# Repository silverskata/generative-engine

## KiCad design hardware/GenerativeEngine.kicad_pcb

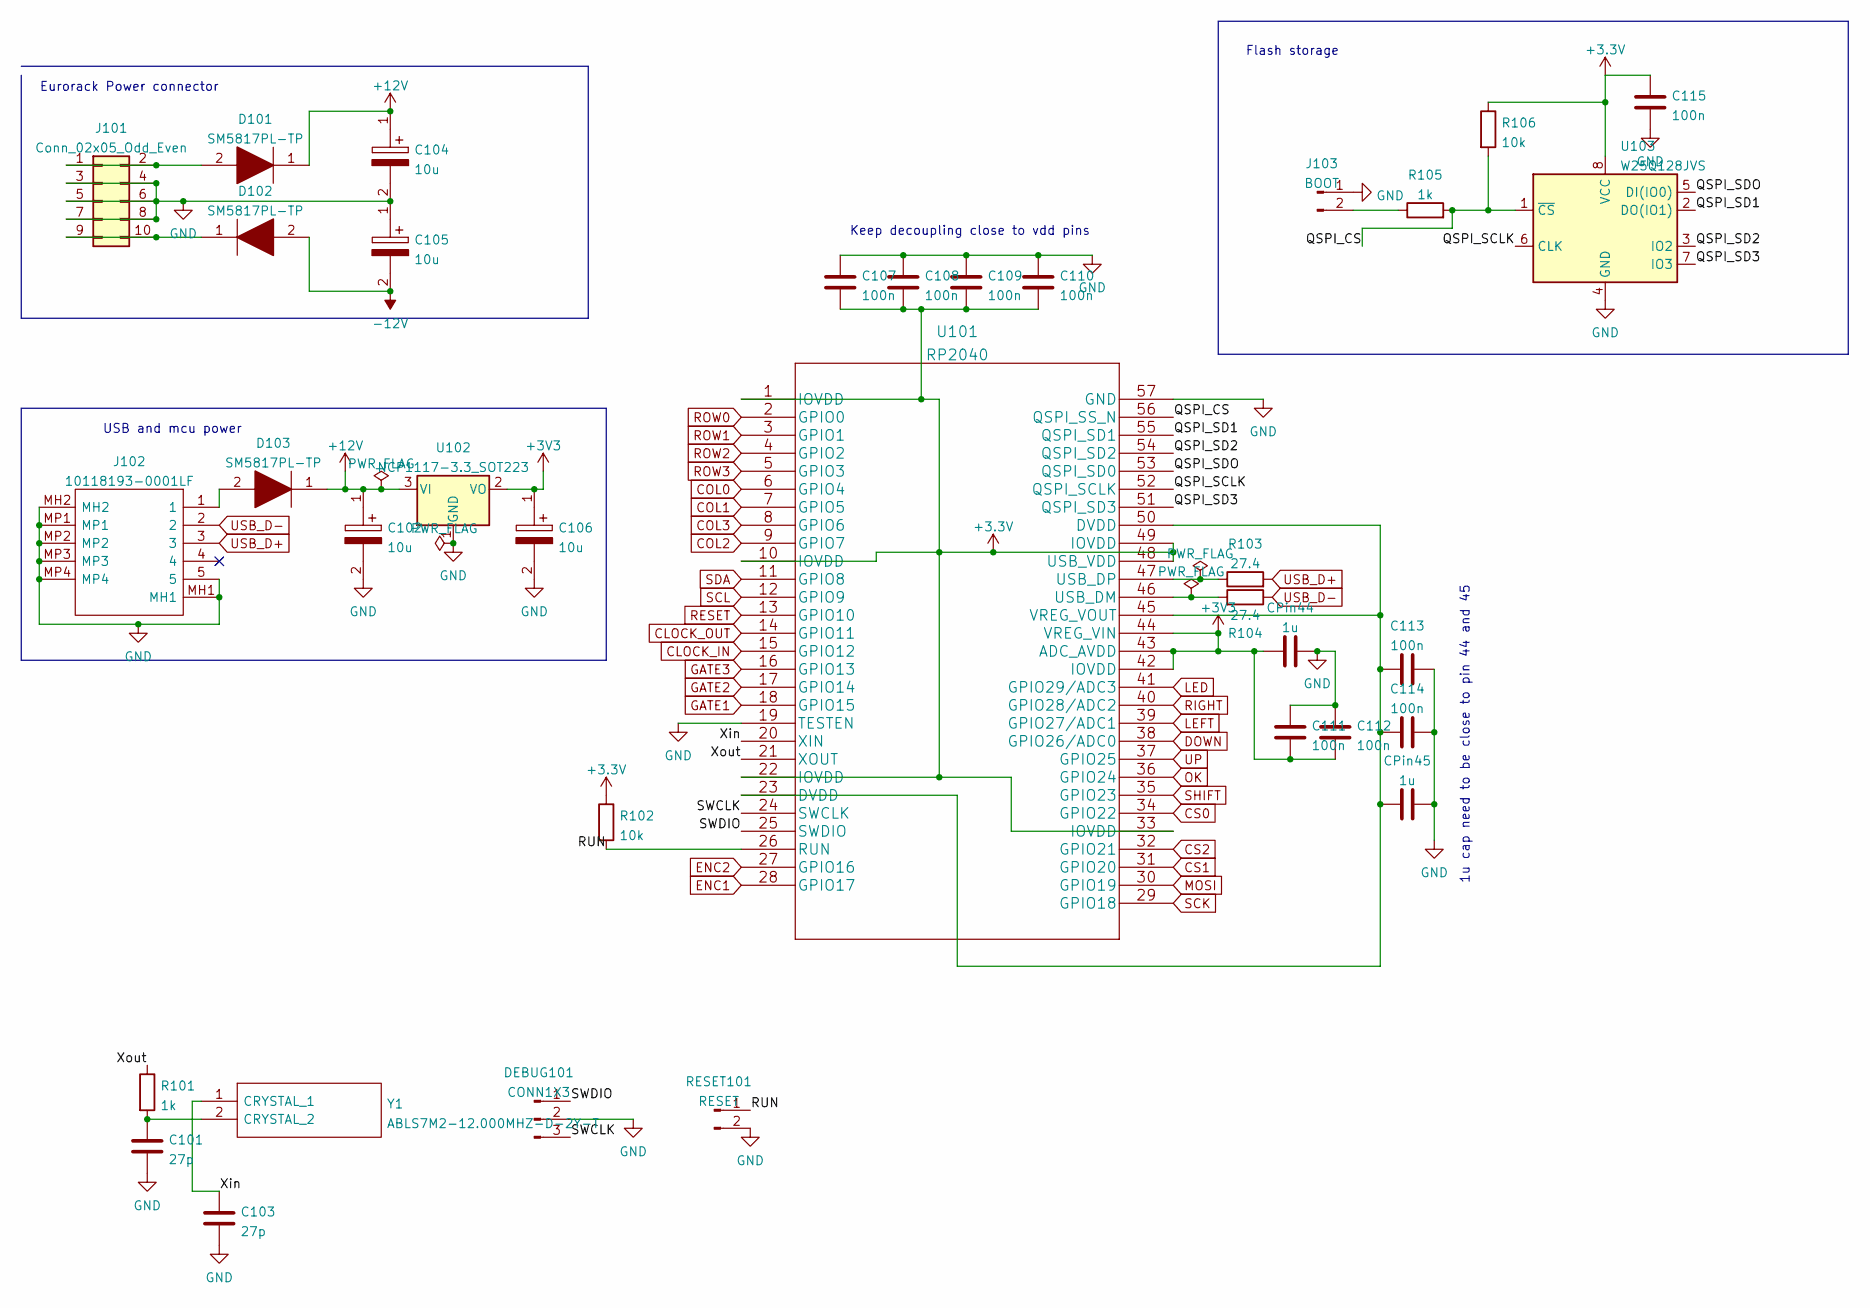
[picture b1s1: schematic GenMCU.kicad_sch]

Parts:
C101, C103: 27p; C_0603_1608Metric_Pad1.08x0.95mm_HandSolder
C102, C104, C105, C106: 10u; CAPAE530X550N; Mouser Part Number 710-865230340001
C107, C108, C109, C110, C111, C112, C113, C114, C115: 100n; C_0603_1608Metric_Pad1.08x0.95mm_HandSolder
CPin44, CPin45: 1u; C_0603_1608Metric_Pad1.08x0.95mm_HandSolder
D101, D102, D103: SM5817PL-TP; SOD3716X120N; Mouser Part Number 833-SM5817PL-TP
DEBUG101: CONN1X3; PinSocket_1x03_P2.54mm_Vertical
J101: Conn_02x05_Odd_Even; PinHeader_2x05_P2.54mm_Vertical
J102: 10118193-0001LF; 101181930001LF; Mouser Part Number 649-10118193-0001LF
J103: BOOT; PinHeader_1x02_P2.54mm_Vertical
R101, R105: 1k; R_0603_1608Metric_Pad0.98x0.95mm_HandSolder
R102, R106: 10k; R_0603_1608Metric_Pad0.98x0.95mm_HandSolder
R103, R104: 27.4; R_0603_1608Metric_Pad0.98x0.95mm_HandSolder
RESET101: RESET; PinHeader_1x02_P2.54mm_Vertical
U101: RP2040
U102: NCP1117-3.3_SOT223; SOT-223-3_TabPin2
U103: W25Q128JVS; SOIC-8_5.23x5.23mm_P1.27mm
Y1: ABLS7M2-12.000MHZ-D-2Y-T; ABLS7M212000MHZD2YT; Mouser Part Number 815-ABLS7M2-12-D-2YT

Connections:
+12V: C102.1, C104.1, D101.1, D103.1, U102.3 (VI); also elsewhere on the board
-12V: C105.2, D102.2; also elsewhere on the board
/GenMCU/QSPI_CS: R105.2, R106.2, U101.56 (QSPI_SS_N), U103.1 (~CS)
/GenMCU/QSPI_SCLK: U101.52 (QSPI_SCLK), U103.6 (CLK)
/GenMCU/QSPI_SD1: U101.55 (QSPI_SD1), U103.2 (DO(IO1))
/GenMCU/QSPI_SD2: U101.54 (QSPI_SD2), U103.3 (IO2)
/GenMCU/QSPI_SD3: U101.51 (QSPI_SD3), U103.7 (IO3)
/GenMCU/QSPI_SDO: U101.53 (QSPI_SD0), U103.5 (DI(IO0))
/GenMCU/RUN: R102.2, RESET101.1, U101.26 (RUN); also elsewhere on the board
/GenMCU/SWCLK: DEBUG101.3, U101.24 (SWCLK); also elsewhere on the board
/GenMCU/SWDIO: DEBUG101.1, U101.25 (SWDIO); also elsewhere on the board
/GenMCU/Xin: C103.1, U101.20 (XIN), Y1.1 (CRYSTAL)
/GenMCU/Xout: R101.1, U101.21 (XOUT)
CLOCK_IN: U101.15 (GPIO12); also elsewhere on the board
CLOCK_OUT: U101.14 (GPIO11); also elsewhere on the board
COL0: U101.6 (GPIO4); also elsewhere on the board
COL1: U101.7 (GPIO5); also elsewhere on the board
COL2: U101.9 (GPIO7); also elsewhere on the board
COL3: U101.8 (GPIO6); also elsewhere on the board
CS0: U101.34 (GPIO22); also elsewhere on the board
CS1: U101.31 (GPIO20); also elsewhere on the board
CS2: U101.32 (GPIO21); also elsewhere on the board
DOWN: U101.38 (GPIO26/ADC0); also elsewhere on the board
ENC1: U101.28 (GPIO17); also elsewhere on the board
ENC2: U101.27 (GPIO16); also elsewhere on the board
GATE1: U101.18 (GPIO15); also elsewhere on the board
GATE2: U101.17 (GPIO14); also elsewhere on the board
GATE3: U101.16 (GPIO13); also elsewhere on the board
GND: C101.2, C102.2, C103.2, C104.2, C105.1, C106.2, C107.1, C108.1, C109.1, C110.1, C111.1, C112.1, C113.2, C114.2, C115.2, CPin44.2, CPin45.2, DEBUG101.2, J101.3, J101.4, J101.5, J101.6, J101.7, J101.8, J102.5, J102.MH1, J102.MH2, J102.MP1, J102.MP2, J102.MP3, J102.MP4, J103.1, RESET101.2, U101.19 (TESTEN), U101.57 (GND), U102.1 (GND), U103.4 (GND); also elsewhere on the board
LED: U101.41 (GPIO29/ADC3); also elsewhere on the board
LEFT: U101.39 (GPIO27/ADC1); also elsewhere on the board
MOSI: U101.30 (GPIO19); also elsewhere on the board
unnamed: C101.1, R101.2, Y1.2 (CRYSTAL)
unnamed: C113.1, C114.1, CPin45.1, U101.23 (DVDD), U101.45 (VREG_VOUT), U101.50 (DVDD)
unnamed: D101.2, J101.1, J101.2
unnamed: D102.1, J101.9, J101.10
unnamed: D103.2, J102.1
unnamed 67: J103.2, R105.1; also elsewhere on the board
unnamed: R103.1, U101.47 (USB_DP)
unnamed: R104.2, U101.46 (USB_DM)
OK: U101.36 (GPIO24); also elsewhere on the board
RESET: U101.13 (GPIO10); also elsewhere on the board
RIGHT: U101.40 (GPIO28/ADC2); also elsewhere on the board
ROW0: U101.2 (GPIO0); also elsewhere on the board
ROW1: U101.3 (GPIO1); also elsewhere on the board
ROW2: U101.4 (GPIO2); also elsewhere on the board
ROW3: U101.5 (GPIO3); also elsewhere on the board
SCK: U101.29 (GPIO18); also elsewhere on the board
SCL: U101.12 (GPIO9); also elsewhere on the board
SDA: U101.11 (GPIO8); also elsewhere on the board
SHIFT: U101.35 (GPIO23); also elsewhere on the board
UP: U101.37 (GPIO25); also elsewhere on the board
USB_D+: J102.3, R103.2
USB_D-: J102.2, R104.1

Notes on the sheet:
USB and mcu power
1u cap need to be close to pin 44 and 45
Flash storage
Eurorack Power connector
Keep decoupling close to vdd pins

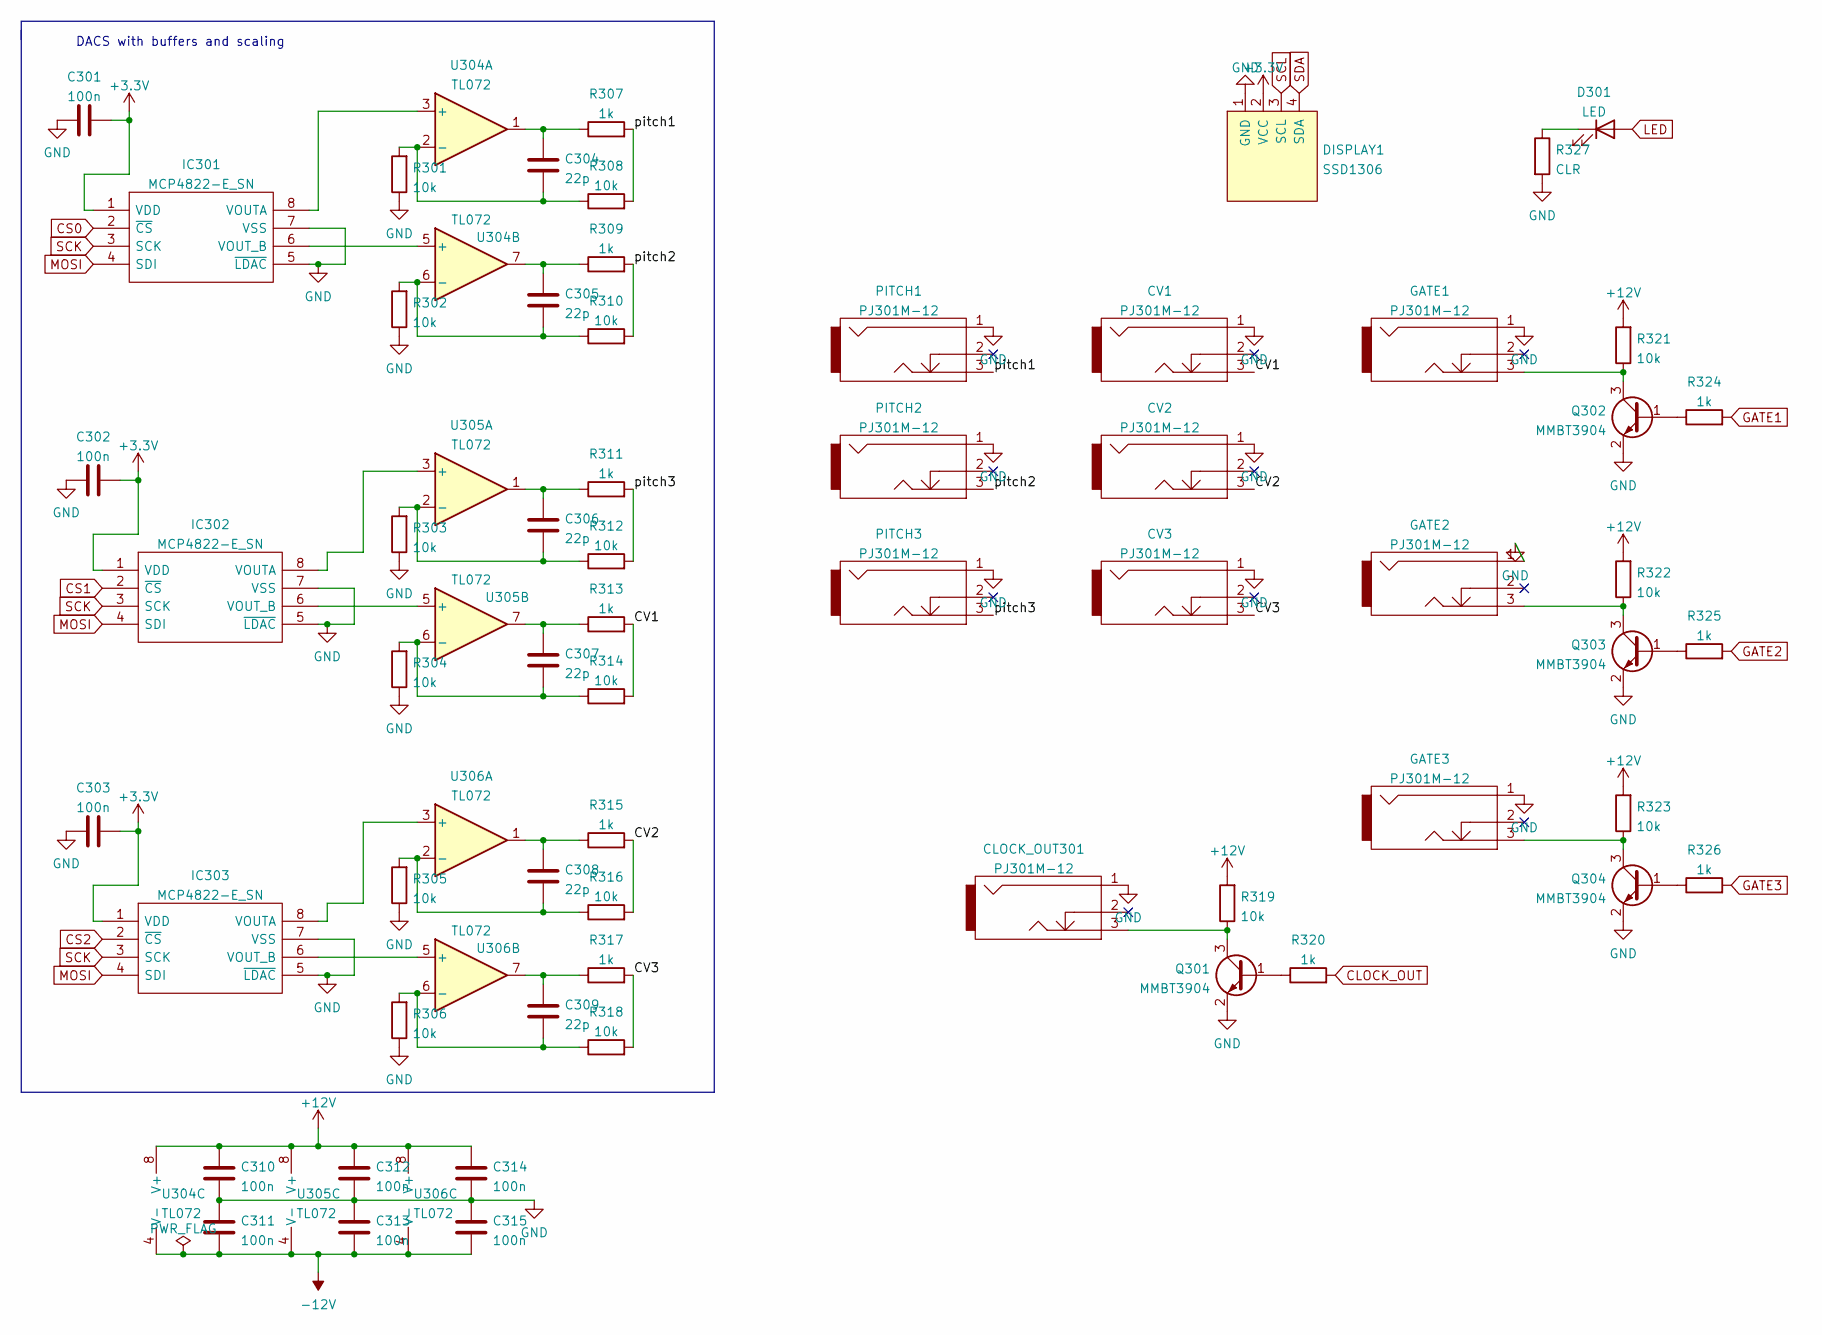
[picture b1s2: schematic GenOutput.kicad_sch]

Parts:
C301, C302, C303, C310, C311, C312, C313, C314, C315: 100n; C_0603_1608Metric_Pad1.08x0.95mm_HandSolder
C304, C305, C306, C307, C308, C309: 22p; C_0603_1608Metric_Pad1.08x0.95mm_HandSolder
CLOCK_OUT301: PJ301M-12
CV1, CV2, CV3: PJ301M-12
D301: LED; LED_D3.0mm
DISPLAY1: SSD1306; 128x64OLED
GATE1, GATE2, GATE3: PJ301M-12
IC301, IC302, IC303: MCP4822-E_SN; SOIC127P600X175-8N; Mouser Part Number 579-MCP4822-E/SN
PITCH1, PITCH2, PITCH3: PJ301M-12
Q301, Q302, Q303, Q304: MMBT3904; SOT-23
R301, R302, R303, R304, R305, R306, R308, R310, R312, R314, R316, R318, R319, R321, R322, R323: 10k; R_0603_1608Metric_Pad0.98x0.95mm_HandSolder
R307, R309, R311, R313, R315, R317, R320, R324, R325, R326: 1k; R_0603_1608Metric_Pad0.98x0.95mm_HandSolder
R327: CLR; R_0603_1608Metric_Pad0.98x0.95mm_HandSolder
U304, U305, U306: TL072; SOIC-8_3.9x4.9mm_P1.27mm

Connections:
+12V: C310.1, C312.1, C314.1, R319.2, R321.2, R322.2, R323.2, U304.8 (V+), U305.8 (V+), U306.8 (V+); also elsewhere on the board
-12V: C311.2, C313.2, C315.2, U304.4 (V-), U305.4 (V-), U306.4 (V-); also elsewhere on the board
/GenOutput/CV1: CV1.3, R313.2, R314.2
/GenOutput/CV2: CV2.3, R315.2, R316.2
/GenOutput/CV3: CV3.3, R317.2, R318.2
/GenOutput/pitch1: PITCH1.3, R307.2, R308.2
/GenOutput/pitch2: PITCH2.3, R309.2, R310.2
/GenOutput/pitch3: PITCH3.3, R311.2, R312.2
CLOCK_OUT: R320.2; also elsewhere on the board
CS0: IC301.2 (~CS); also elsewhere on the board
CS1: IC302.2 (~CS); also elsewhere on the board
CS2: IC303.2 (~CS); also elsewhere on the board
GATE1: R324.2; also elsewhere on the board
GATE2: R325.2; also elsewhere on the board
GATE3: R326.2; also elsewhere on the board
GND: C301.1, C302.1, C303.1, C310.2, C311.1, C312.2, C313.1, C314.2, C315.1, CLOCK_OUT301.1, CV1.1, CV2.1, CV3.1, DISPLAY1.1 (GND), GATE1.1, GATE2.1, GATE3.1, IC301.5 (~LDAC), IC301.7 (VSS), IC302.5 (~LDAC), IC302.7 (VSS), IC303.5 (~LDAC), IC303.7 (VSS), PITCH1.1, PITCH2.1, PITCH3.1, Q301.2 (E), Q302.2 (E), Q303.2 (E), Q304.2 (E), R301.1, R302.1, R303.1, R304.1, R305.1, R306.1, R327.2; also elsewhere on the board
LED: D301.2 (A); also elsewhere on the board
MOSI: IC301.4 (SDI), IC302.4 (SDI), IC303.4 (SDI); also elsewhere on the board
unnamed: C304.1, R307.1, U304.1
unnamed: C304.2, R301.2, R308.1, U304.2 (-)
unnamed: C305.1, R309.1, U304.7
unnamed: C305.2, R302.2, R310.1, U304.6 (-)
unnamed: C306.1, R311.1, U305.1
unnamed: C306.2, R303.2, R312.1, U305.2 (-)
unnamed: C307.1, R313.1, U305.7
unnamed: C307.2, R304.2, R314.1, U305.6 (-)
unnamed: C308.1, R315.1, U306.1
unnamed: C308.2, R305.2, R316.1, U306.2 (-)
unnamed: C309.1, R317.1, U306.7
unnamed: C309.2, R306.2, R318.1, U306.6 (-)
unnamed 53: CLOCK_OUT301.3, Q301.3 (C), R319.1; also elsewhere on the board
unnamed: D301.1 (K), R327.1
unnamed: GATE1.3, Q302.3 (C), R321.1
unnamed: GATE2.3, Q303.3 (C), R322.1
unnamed: GATE3.3, Q304.3 (C), R323.1
unnamed: IC301.6 (VOUT_B), U304.5 (+)
unnamed: IC301.8 (VOUTA), U304.3 (+)
unnamed: IC302.6 (VOUT_B), U305.5 (+)
unnamed: IC302.8 (VOUTA), U305.3 (+)
unnamed: IC303.6 (VOUT_B), U306.5 (+)
unnamed: IC303.8 (VOUTA), U306.3 (+)
unnamed: Q301.1 (B), R320.1
unnamed: Q302.1 (B), R324.1
unnamed: Q303.1 (B), R325.1
unnamed: Q304.1 (B), R326.1
SCK: IC301.3 (SCK), IC302.3 (SCK), IC303.3 (SCK); also elsewhere on the board

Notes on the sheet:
DACS with buffers and scaling

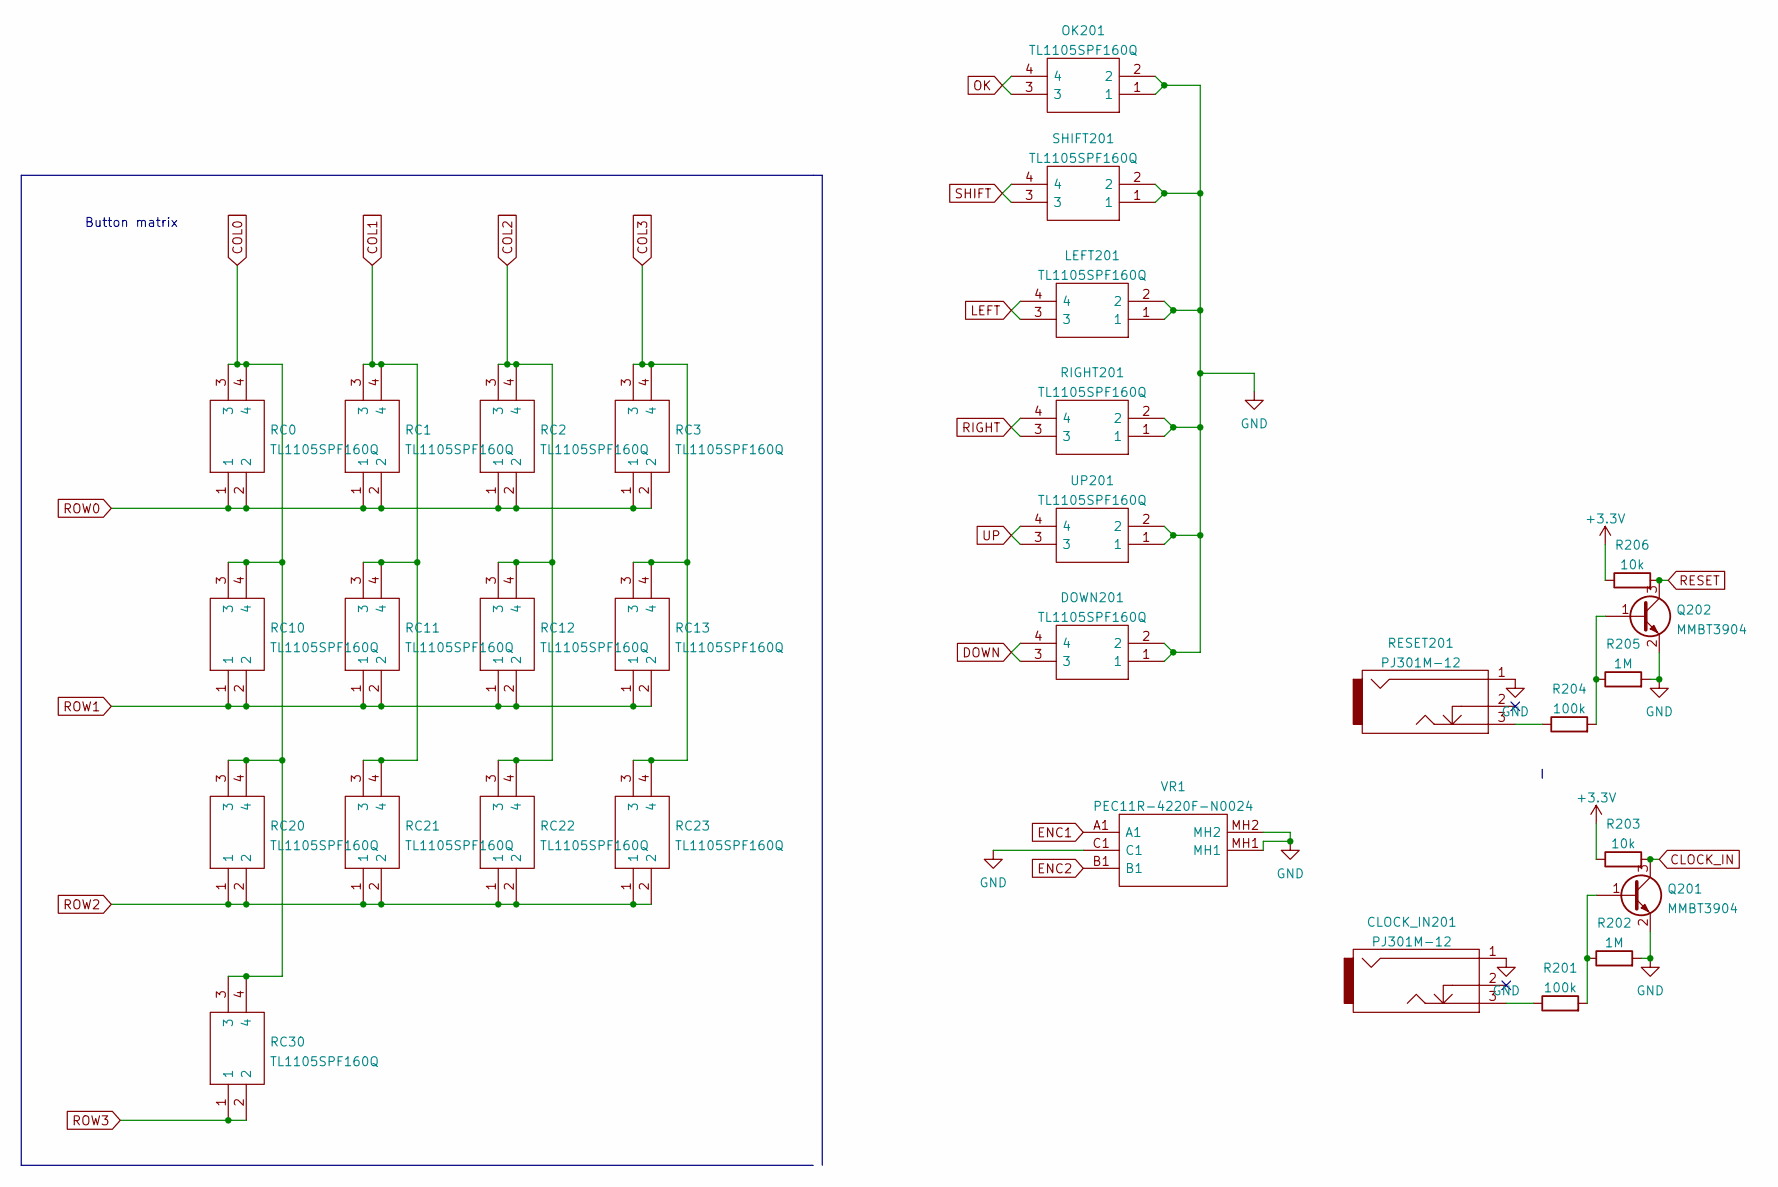
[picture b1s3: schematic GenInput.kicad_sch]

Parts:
CLOCK_IN201: PJ301M-12
DOWN201: TL1105SPF160Q; Mouser Part Number 612-TL1105SP
LEFT201: TL1105SPF160Q; Mouser Part Number 612-TL1105SP
OK201: TL1105SPF160Q; Mouser Part Number 612-TL1105SP
Q201, Q202: MMBT3904; SOT-23
R201, R204: 100k; R_0603_1608Metric_Pad0.98x0.95mm_HandSolder
R202, R205: 1M; R_0603_1608Metric_Pad0.98x0.95mm_HandSolder
R203, R206: 10k; R_0603_1608Metric_Pad0.98x0.95mm_HandSolder
RC0, RC1, RC2, RC3, RC10, RC11, RC12, RC13, RC20, RC21, RC22, RC23, RC30: TL1105SPF160Q; Mouser Part Number 612-TL1105SP
RESET201: PJ301M-12
RIGHT201: TL1105SPF160Q; Mouser Part Number 612-TL1105SP
SHIFT201: TL1105SPF160Q; Mouser Part Number 612-TL1105SP
UP201: TL1105SPF160Q; Mouser Part Number 612-TL1105SP
VR1: PEC11R-4220F-N0024; PEC11R4215FN0012; Mouser Part Number 652-PEC11R-4220F-N24

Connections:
CLOCK_IN: Q201.3 (C), R203.2; also elsewhere on the board
COL0: RC0.3, RC0.4, RC10.3, RC10.4, RC20.3, RC20.4, RC30.3, RC30.4; also elsewhere on the board
COL1: RC1.3, RC1.4, RC11.3, RC11.4, RC21.3, RC21.4; also elsewhere on the board
COL2: RC2.3, RC2.4, RC12.3, RC12.4, RC22.3, RC22.4; also elsewhere on the board
COL3: RC3.3, RC3.4, RC13.3, RC13.4, RC23.3, RC23.4; also elsewhere on the board
DOWN: DOWN201.3, DOWN201.4; also elsewhere on the board
GND: CLOCK_IN201.1, DOWN201.1, DOWN201.2, LEFT201.1, LEFT201.2, OK201.1, OK201.2, Q201.2 (E), Q202.2 (E), R202.2, R205.2, RESET201.1, RIGHT201.1, RIGHT201.2, SHIFT201.1, SHIFT201.2, UP201.1, UP201.2, VR1.C1, VR1.MH1, VR1.MH2; also elsewhere on the board
LEFT: LEFT201.3, LEFT201.4; also elsewhere on the board
unnamed 52: CLOCK_IN201.3, R201.1; also elsewhere on the board
unnamed: Q201.1 (B), R201.2, R202.1
unnamed: Q202.1 (B), R204.2, R205.1
unnamed: R204.1, RESET201.3
OK: OK201.3, OK201.4; also elsewhere on the board
RESET: Q202.3 (C), R206.2; also elsewhere on the board
RIGHT: RIGHT201.3, RIGHT201.4; also elsewhere on the board
ROW0: RC0.1, RC0.2, RC1.1, RC1.2, RC2.1, RC2.2, RC3.1, RC3.2; also elsewhere on the board
ROW1: RC10.1, RC10.2, RC11.1, RC11.2, RC12.1, RC12.2, RC13.1, RC13.2; also elsewhere on the board
ROW2: RC20.1, RC20.2, RC21.1, RC21.2, RC22.1, RC22.2, RC23.1, RC23.2; also elsewhere on the board
ROW3: RC30.1, RC30.2; also elsewhere on the board
SHIFT: SHIFT201.3, SHIFT201.4; also elsewhere on the board
UP: UP201.3, UP201.4; also elsewhere on the board

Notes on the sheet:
Button matrix

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
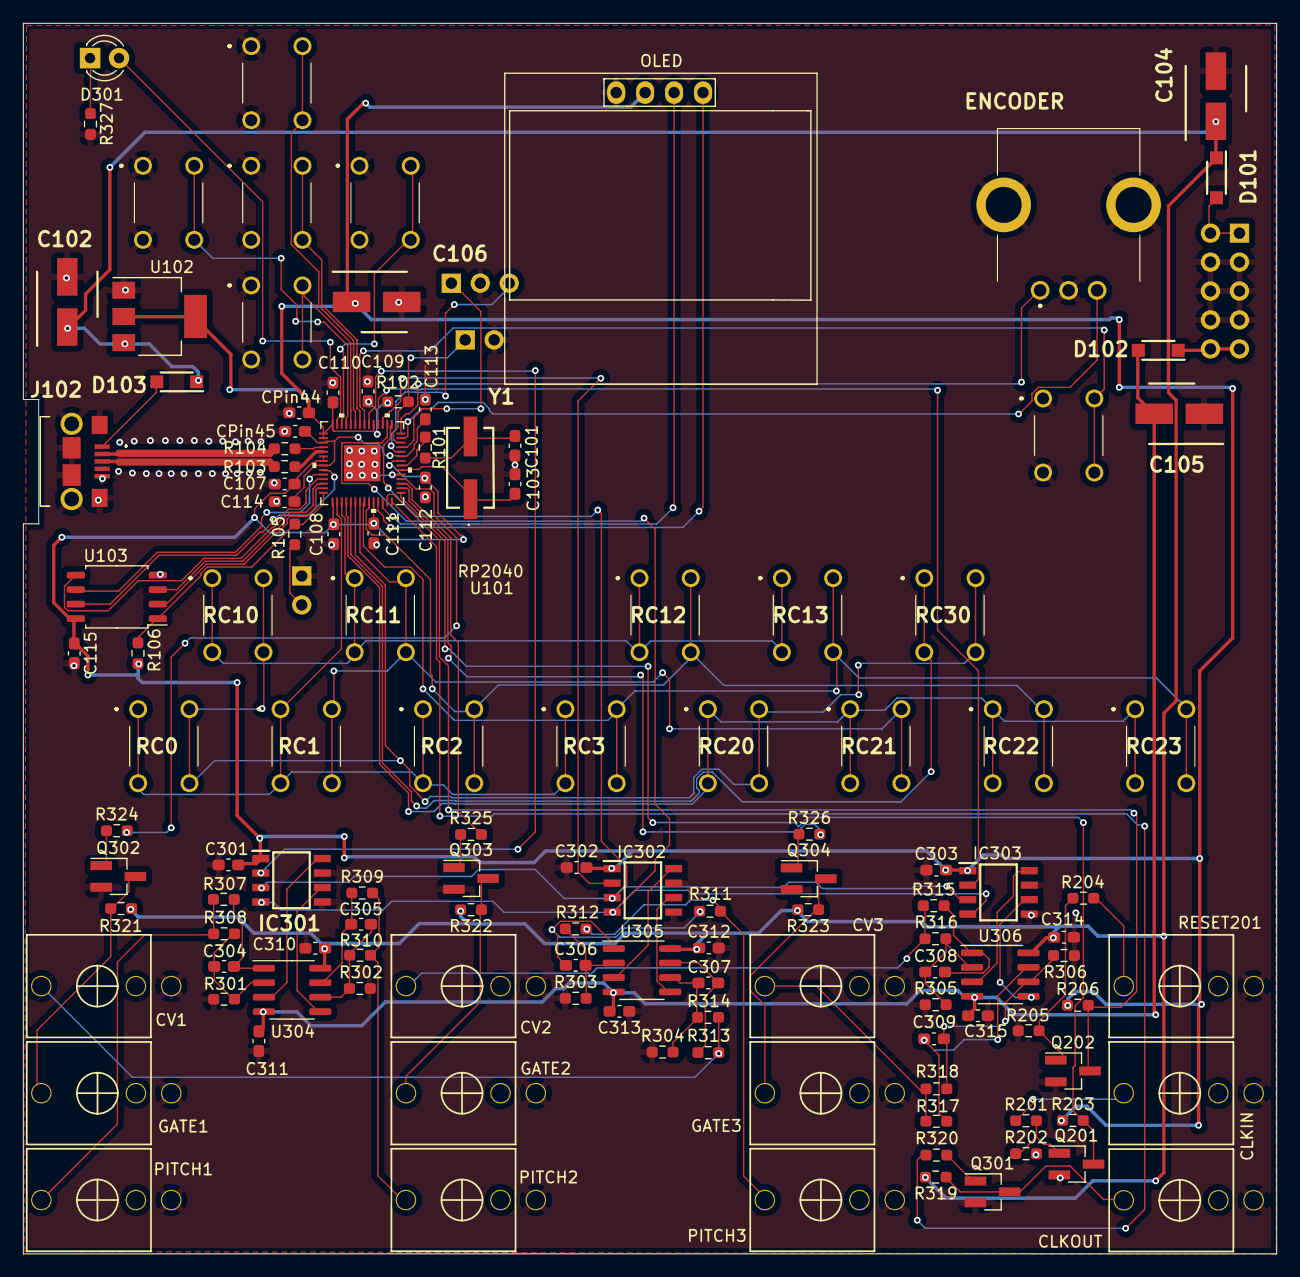
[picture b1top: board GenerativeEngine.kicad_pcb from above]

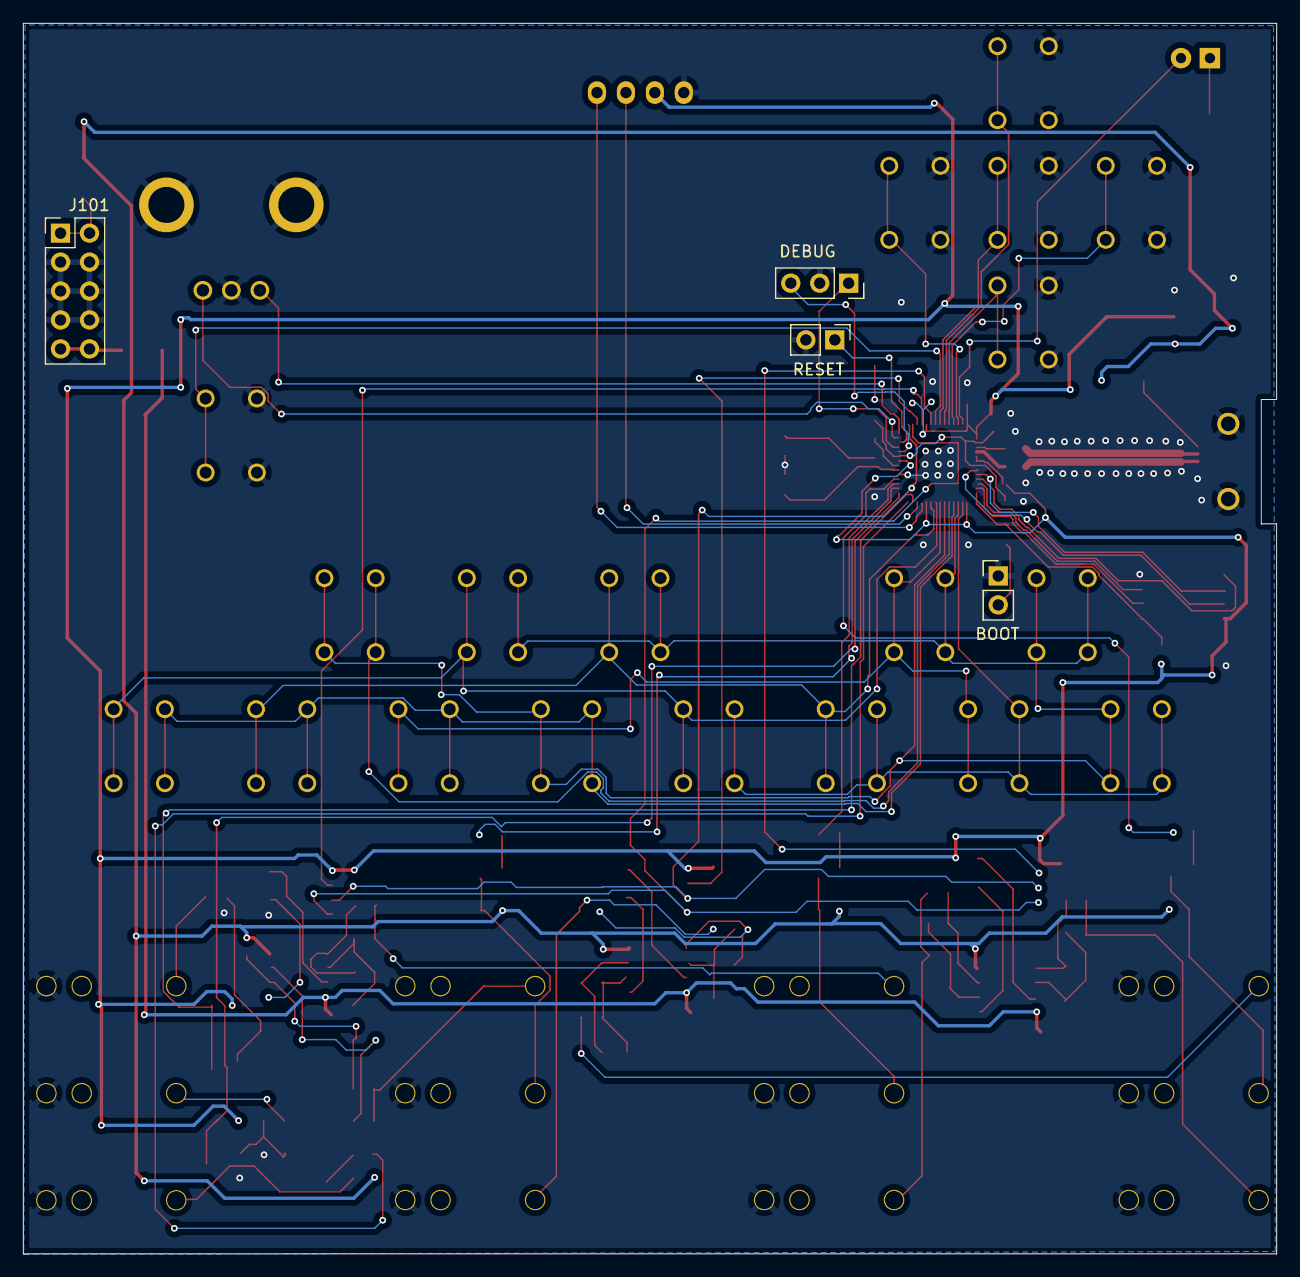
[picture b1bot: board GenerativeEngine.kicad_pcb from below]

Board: 2 copper layers, 110.0 x 108.0 mm, 129 parts (4 on the bottom side), 92 nets.

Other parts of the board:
BOOT: BOOT; PinHeader_1x02_P2.54mm_Vertical
CLKIN: PJ301M-12
CLKOUT: PJ301M-12
DEBUG: CONN1X3; PinSocket_1x03_P2.54mm_Vertical
ENCODER: PEC11R-4220F-N0024; PEC11R4215FN0012
OLED: SSD1306; 128x64OLED
RESET: RESET; PinHeader_1x02_P2.54mm_Vertical

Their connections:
/GenMCU/RUN: RESET.1; also elsewhere on the board
/GenMCU/SWCLK: DEBUG.3; also elsewhere on the board
/GenMCU/SWDIO: DEBUG.1; also elsewhere on the board
ENC1: ENCODER.A1; also elsewhere on the board
ENC2: ENCODER.B1; also elsewhere on the board
GND: BOOT.1, CLKIN.1, CLKOUT.1, DEBUG.2, ENCODER.C1, ENCODER.MH1, ENCODER.MH2, OLED.1 (GND), RESET.2; also elsewhere on the board
unnamed 52: CLKIN.3; also elsewhere on the board
unnamed 53: CLKOUT.3; also elsewhere on the board
unnamed 67: BOOT.2; also elsewhere on the board
SCL: OLED.3 (SCL); also elsewhere on the board
SDA: OLED.4 (SDA); also elsewhere on the board

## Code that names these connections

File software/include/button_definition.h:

// BUTTONS
#define RIGHT 28
#define LEFT 27
#define UP 25
#define OK 24
#define DOWN 26
#define ROW0 0
#define ROW1 1
#define ROW2 2
#define ROW3 3
#define COL0 4
#define COL1 5
#define COL2 6
#define COL3 7
#define SHIFT 23
#define BUTTON_C 17
#define BUTTON_C_SHARP 33
#define BUTTON_D 18
#define BUTTON_D_SHARP 34
#define BUTTON_E 24
#define BUTTON_F 20
#define BUTTON_F_SHARP 40
#define BUTTON_G 65
#define BUTTON_G_SHARP 36
#define BUTTON_A 66
#define BUTTON_B_FLAT 129
#define BUTTON_B 72
#define BUTTON_REST 68
#define BUTTON_LEFT 0x01
#define BUTTON_RIGHT 0x02
#define BUTTON_UP 0x04
#define BUTTON_DOWN 0x08
#define BUTTON_OK 0x10
#define BUTTON_SHIFT 0x20
#define KEYBOARD_ONE 0x0001
#define KEYBOARD_TWO 0x0002
#define KEYBOARD_THREE 0x0004
#define KEYBOARD_FOUR 0x0008
#define KEYBOARD_FIVE 0x0010
#define KEYBOARD_SIX 0x0020
#define KEYBOARD_SEVEN 0x0040
#define KEYBOARD_EIGHT 0x0080
#define KEYBOARD_NINE 0x0100
#define KEYBOARD_TEN 0x0200
#define KEYBOARD_ELEVEN 0x0400
#define KEYBOARD_TVELVE 0x0800
#define KEYBOARD_THIRTEEN 0x1000

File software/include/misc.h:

#include "stdint.h"

#define GATE1 15
#define GATE2 14
#define GATE3 13
#define GATE_ON 0
#define GATE_OFF 1

void output_setup();

void flash_led(uint8_t times, uint32_t duration_ms);

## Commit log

2022-05-01 Hardware version 1.0
2022-05-01 First software commit
2022-05-17 Sequencer completed
2022-05-17 removed surplus files
2022-05-18 edit UI fix
2022-05-18 bar length automated
2022-05-18 gitignore updated
2022-05-22 Random generation first commit
2022-05-27 Generation complete, UI updated
2022-05-28 Generation UI and logic fixed
2022-05-28 Delay cycle fixed
2022-05-31 Scale generation (finally) fixed
